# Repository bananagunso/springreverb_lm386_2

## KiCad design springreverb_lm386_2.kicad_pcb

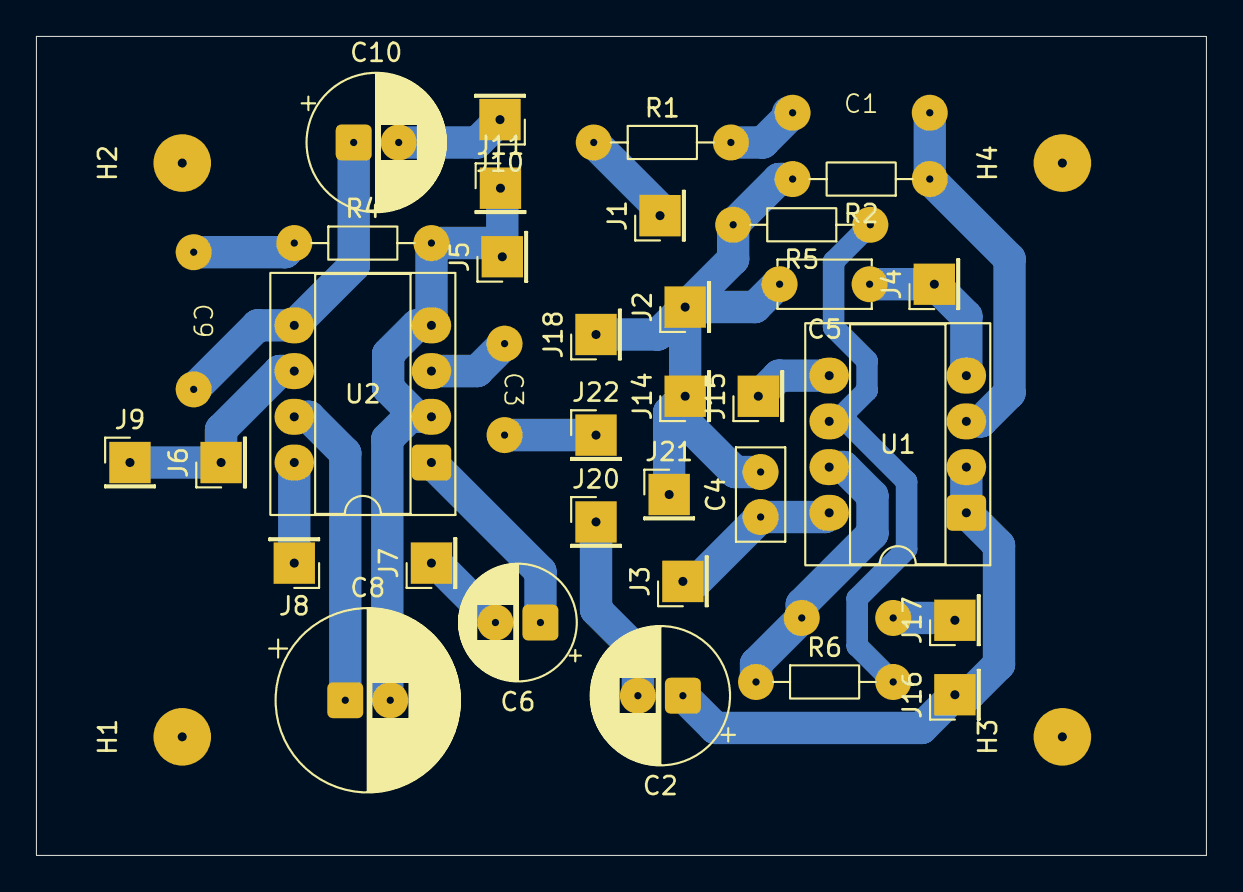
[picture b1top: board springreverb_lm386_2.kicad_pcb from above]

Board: 2 copper layers, 65.0 x 45.5 mm, 40 parts (0 on the bottom side), 23 nets.

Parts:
C1: 0.1u; 9.3_4.3_p7.5
C2, C10: 100u; CP_Radial_D7.5mm_P2.50mm
C3, C11: 820p; 7.5_3.5_p5.0
C4: 0.1u; C_Disc_D5.0mm_W2.5mm_P2.50mm
C5: 0.1u; C_Disc_D5.0mm_W2.5mm_P5.00mm
C6: 10u; CP_Radial_D6.3mm_P2.50mm
C8: 100u; CP_Radial_D10.0mm_P2.50mm
C9: 0.047u; 9.3_4.3_p7.5
H1, H2, H3, H4: MountingHole; MountingHole_3.2mm_M3
J1: IN; PinHeader_1x01_P2.54mm_Vertical
J2: IN_GND; PinHeader_1x01_P2.54mm_Vertical
J3: +15v; PinHeader_1x01_P2.54mm_Vertical
J4: -15v; PinHeader_1x01_P2.54mm_Vertical
J5: GND2; PinHeader_1x01_P2.54mm_Vertical
J6: +15v2; PinHeader_1x01_P2.54mm_Vertical
J7, J17: VR2_3; PinHeader_1x01_P2.54mm_Vertical
J8: VR2_2; PinHeader_1x01_P2.54mm_Vertical
J9: +15vLED; PinHeader_1x01_P2.54mm_Vertical
J10: To; PinHeader_1x01_P2.54mm_Vertical
J11: ToGND; PinHeader_1x01_P2.54mm_Vertical
J14: FromGND; PinHeader_1x01_P2.54mm_Vertical
J15: From; PinHeader_1x01_P2.54mm_Vertical
J16: VR2_1; PinHeader_1x01_P2.54mm_Vertical
J18: OUT_GND; PinHeader_1x01_P2.54mm_Vertical
J20: VR1_3; PinHeader_1x01_P2.54mm_Vertical
J21: VR1_1; PinHeader_1x01_P2.54mm_Vertical
J22: VR1_2; PinHeader_1x01_P2.54mm_Vertical
R1: 10k; R_Axial_DIN0204_L3.6mm_D1.6mm_P7.62mm_Horizontal
R2: 1M; R_Axial_DIN0204_L3.6mm_D1.6mm_P7.62mm_Horizontal
R4: 10; R_Axial_DIN0204_L3.6mm_D1.6mm_P7.62mm_Horizontal
R5: 2.2k; R_Axial_DIN0204_L3.6mm_D1.6mm_P7.62mm_Horizontal
R6: 220k; R_Axial_DIN0204_L3.6mm_D1.6mm_P7.62mm_Horizontal
U1: TL072; CERDIP-8_W7.62mm_SideBrazed_Socket
U2: LM386; CERDIP-8_W7.62mm_SideBrazed_Socket

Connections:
GND1: C4.2, C5.2, J2.1 (Pin_1_1), J14.1 (Pin_1_1), J18.1 (Pin_1_1), J21.1 (Pin_1_1), R2.2, R5.2
GND2: C8.2, J5.1 (Pin_1_1), J11.1 (Pin_1_1), R4.2, U2.2 (-), U2.4 (GND)
unnamed: C1.1, R1.2
unnamed: C6.1, U2.1 (GAIN)
unnamed: C9.1, R4.1
unnamed: C9.2, C10.1, U2.5
unnamed: C11.1, R6.1, U1.7
unnamed: J1.1 (Pin_1_1), R1.1
unnamed: C4.1, J3.1 (Pin_1_1), U1.8 (V+)
unnamed: C5.1, J4.1 (Pin_1_1), U1.4 (V-)
unnamed: J6.1 (Pin_1_1), J9.1 (Pin_1_1), U2.6 (V+)
unnamed: C6.2, J7.1 (Pin_1_1)
unnamed: J8.1 (Pin_1_1), U2.8 (GAIN)
unnamed: C10.2, J10.1 (Pin_1_1)
unnamed: J15.1 (Pin_1_1), U1.5 (+)
unnamed: C2.1, J16.1 (Pin_1_1), U1.1, U1.2 (-)
unnamed: C11.2, J17.1 (Pin_1_1)
unnamed: C2.2, J20.1 (Pin_1_1)
unnamed: C3.2, J22.1 (Pin_1_1)
unnamed: C1.2, R2.1, U1.3 (+)
unnamed: R5.1, R6.2, U1.6 (-)
unnamed: C3.1, U2.3 (+)
unnamed: C8.1, U2.7 (BYPASS)
